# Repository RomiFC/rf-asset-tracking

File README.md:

# rfid-asset-tracking

Realtime asset tracking system utilizing UWB technology and code from Qorvo. This project was initially going to be accomplished with passive tags and an RFID system design but was abandoned due to poor node sensitivity. The new design utilizes Qorvo's MDEK-1001 development boards and multiple Raspberry Pi 3B computers. For more information, see the [official documentation](Documentation/Final%20Report.pdf).

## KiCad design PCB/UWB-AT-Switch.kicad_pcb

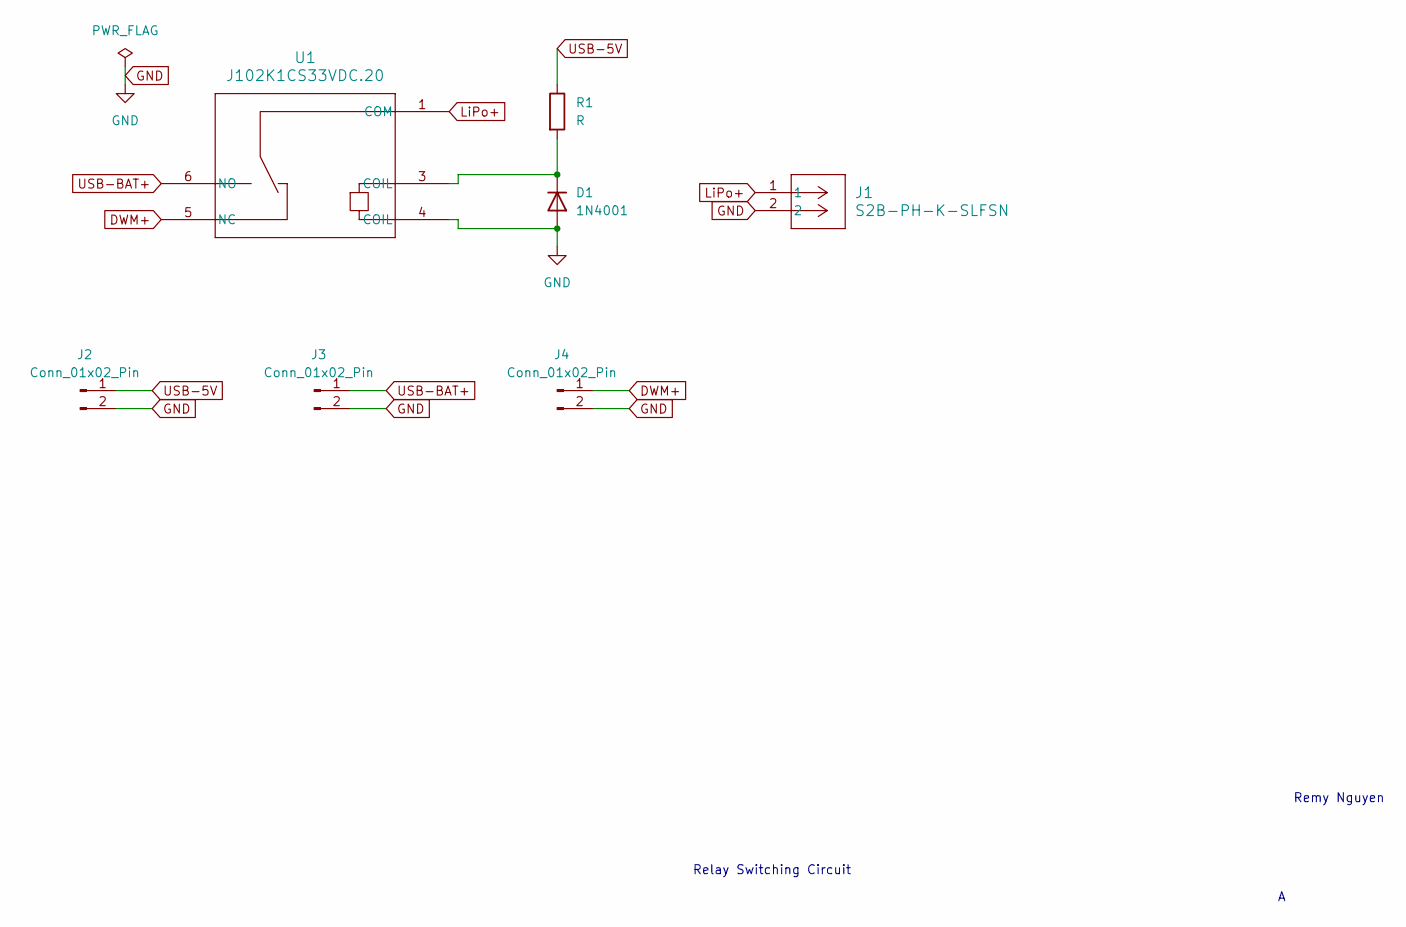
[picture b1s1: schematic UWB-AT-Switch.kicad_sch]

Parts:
D1: 1N4001; D_DO-41_SOD81_P10.16mm_Horizontal
J1: S2B-PH-K-SLFSN; CONN_S2B-PH-K-S_JST
J2, J3, J4: Conn_01x02_Pin; PinHeader_1x02_P2.54mm_Vertical
R1: R; R_Axial_DIN0309_L9.0mm_D3.2mm_P12.70mm_Horizontal
U1: J102K1CS33VDC.20; RELAY8_J102K1CS33VDC.20_CRS

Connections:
DWM+: J4.1, U1.5 (NC)
GND: D1.2 (A), J1.2, J2.2, J3.2, J4.2, U1.4 (COIL)
LiPo+: J1.1, U1.1 (COM)
unnamed: D1.1 (K), R1.2, U1.3 (COIL)
USB-5V: J2.1, R1.1
USB-BAT+: J3.1, U1.6 (NO)

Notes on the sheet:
Relay Switching Circuit
Remy Nguyen

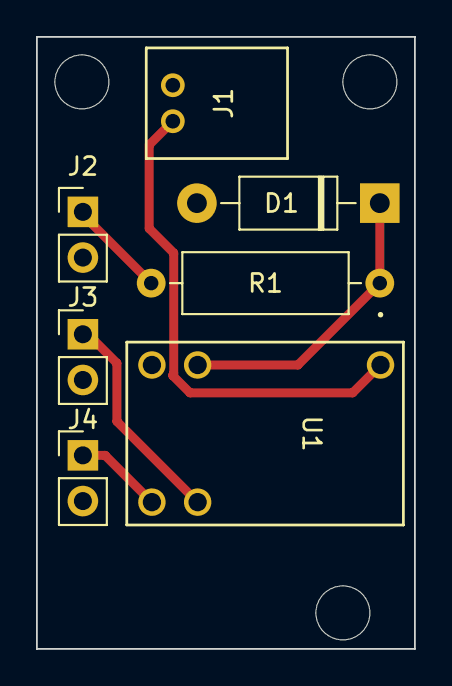
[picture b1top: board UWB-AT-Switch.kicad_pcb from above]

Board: 2 copper layers, 21.0 x 34.0 mm, 7 parts (0 on the bottom side), 6 nets.

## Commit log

2023-04-06 initial local commit
2023-04-06 Added counter for tags scanned. When datalogging, reader will scan until COUNT_MAX tags have been reached, then stop until user inputs to serial monitor.
    OLD CHANGES:
    -Added datalogging function that prints to serial monitor in csv format
    -Intended to be used with a terminal emulator (PuTTY) that saves serial monitor to csv
    -Code compiles but none of this has been tested on the board yet
    -Still no way to input grid coordinates for datalogging
2023-04-06 THIS BUILD KIND OF WORKS MAYBE IDK *THUMBS UP EMOJI* LIKE HALF OF THE PROGRAM IS COMMENTED OUT
2023-04-06 Deleted duplicate directory
2023-04-07 Cleaned up code and removed unnecessary user input. Added time value (since program began) and units to csv header.
2023-04-07 Fixed scan counter to stop when maximum count has been reached (maybe)
2023-04-07 commented out the entire program again because nothing is scanning correctly
2023-04-07 the wire was loose
2023-04-08 reverted old changes and added new constants. The board throttles tx power when it gets too hot, limitting read range
2023-04-08 uncommented everything
2023-04-08 Moved nano.parseResponse() to void loop() to more easily test responses for temperature control
2023-04-08 Added cases for temperature related responses for logging. Difference between TEMPTHROTTLE and TEMPERATURE need to be tested
2023-04-09 Added MATLAB directory
2023-04-11 Added support for ESP32 framework in platformio.ini. Code will not compile yet because ESP32 does not support SoftwareSerial.h.
2023-06-30 Moved directories
2023-07-01 Added new main-uno.cpp and main-esp.cpp for different environments, separated official SparkFun library and new SparkFun_RFID_Custom under PlatformIO/lib
2023-07-01 Added README.md
2023-07-18 Added research and datasheets
2023-09-01 Housekeeping: Custom Sparkfun library is now isolated and free to edit, Nano documentation added
2023-09-01 Added more documentation and research
2023-09-01 Updated .gitignore
2023-09-02 Added rf-fe block diagram
2023-09-07 Added component datasheets
2023-09-09 New rf-fe block diagram design
2023-10-04 RFID on backburner, prep for merge
2023-10-28 pcb rev-a complete
2023-10-28 silkscreen updated
2023-10-31 added 3rd mounting hole
2023-10-31 changes not saved
2023-11-09 added mqtt test
2023-11-10 new parsed python script
    could be parsed more
2023-11-10 Update mqtt test 2.py
    did some parsing, idk if it works tho
2023-11-10 Update mqtt test 2.py
    updated code with parsing
2023-11-11 Mqtt test 3
    Maybe Final, this should do everything needed for the program/script
2023-11-11 Update mqtt test 3.py
    I think this one should be the final, but it may also not be
2023-11-14 new code
    stops errors when cant connect
2023-11-14 added comments to each
2023-11-14 Create mqtt test 5.py
    Work in progress, not done yet
2023-11-14 Create mqtt test bench.py
    This is a test bench for the code so you dont need mqtt
2023-11-29 Changed some variable names
2023-12-14 deleted some stuff
2023-12-14 changed some stuff
2023-12-14 new final
2023-12-14 moved to archive folder
2023-12-14 moved folder
2024-01-22 Added expo documentation
